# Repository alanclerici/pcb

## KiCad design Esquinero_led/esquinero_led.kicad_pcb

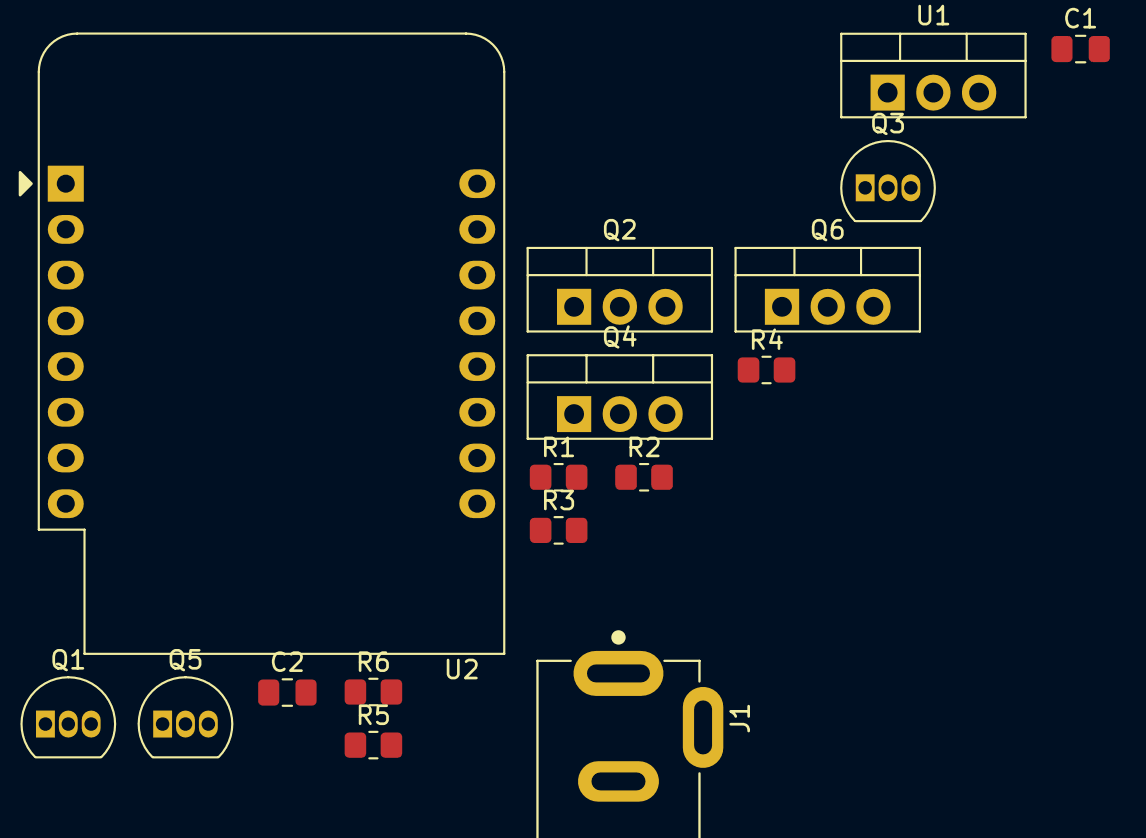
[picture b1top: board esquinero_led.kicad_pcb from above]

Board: 2 copper layers, 17 parts (0 on the bottom side), 9 nets, no tracks yet.

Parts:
C1, C2: 10uF; C_0805_2012Metric_Pad1.18x1.45mm_HandSolder
J1: PJ-002B; CUI_PJ-002B
Q1, Q3, Q5: BC548; TO-92_Inline
Q2, Q4, Q6: IRF540N; TO-220-3_Vertical
R1, R2, R3, R4, R5, R6: 10K; R_0805_2012Metric_Pad1.20x1.40mm_HandSolder
U1: LM7805_TO220; TO-220-3_Vertical
U2: WeMos_D1_mini; WEMOS_D1_mini_light

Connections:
+5V: C2.1, U1.3 (VO), U2.9 (5V)
+12V: C1.1, J1.1, R2.2, R4.2, R6.2, U1.1 (VI)
GND: C1.2, C2.2, J1.2, Q1.3 (E), Q2.3 (S), Q3.3 (E), Q4.3 (S), Q5.3 (E), Q6.3 (S), U1.2 (GND), U2.10 (GND)
unnamed: Q1.1 (C), Q2.1 (G), R2.1
unnamed: Q1.2 (B), R1.2
unnamed: Q3.1 (C), Q4.1 (G), R4.1
unnamed: Q3.2 (B), R3.2
unnamed: Q5.1 (C), Q6.1 (G), R6.1
unnamed: Q5.2 (B), R5.2

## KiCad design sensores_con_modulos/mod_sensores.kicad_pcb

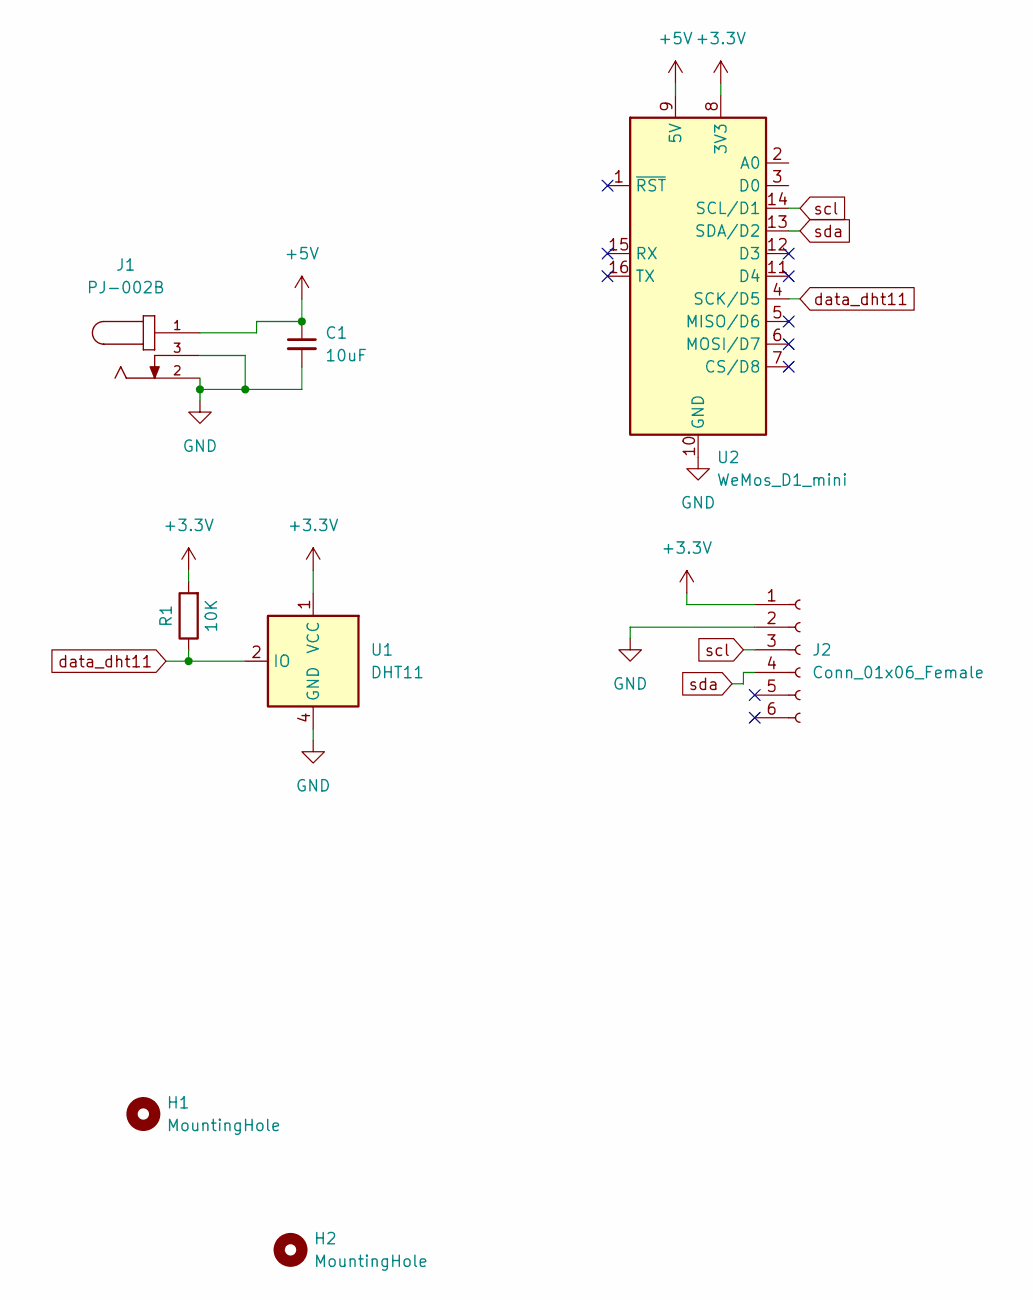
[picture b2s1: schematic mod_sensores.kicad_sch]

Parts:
C1: 10uF; CP_Radial_D5.0mm_P2.50mm
H1, H2: MountingHole; MountingHole_2.5mm
J1: PJ-002B; CUI_PJ-002B
J2: Conn_01x06_Female; PinHeader_1x06_P2.54mm_Vertical
R1: 10K; R_Axial_DIN0207_L6.3mm_D2.5mm_P7.62mm_Horizontal
U1: DHT11; Aosong_DHT11_5.5x12.0_P2.54mm
U2: WeMos_D1_mini; WEMOS_D1_mini_light

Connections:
+3.3V: J2.1, R1.2, U1.1 (VCC), U2.8 (3V3)
+5V: C1.1, J1.1, U2.9 (5V)
GND: C1.2, J1.2, J1.3, J2.2, U1.4 (GND), U2.10 (GND)
data_dht11: R1.1, U1.2 (IO), U2.4 (SCK/D5)
scl: J2.3, U2.14 (SCL/D1)
sda: J2.4, U2.13 (SDA/D2)

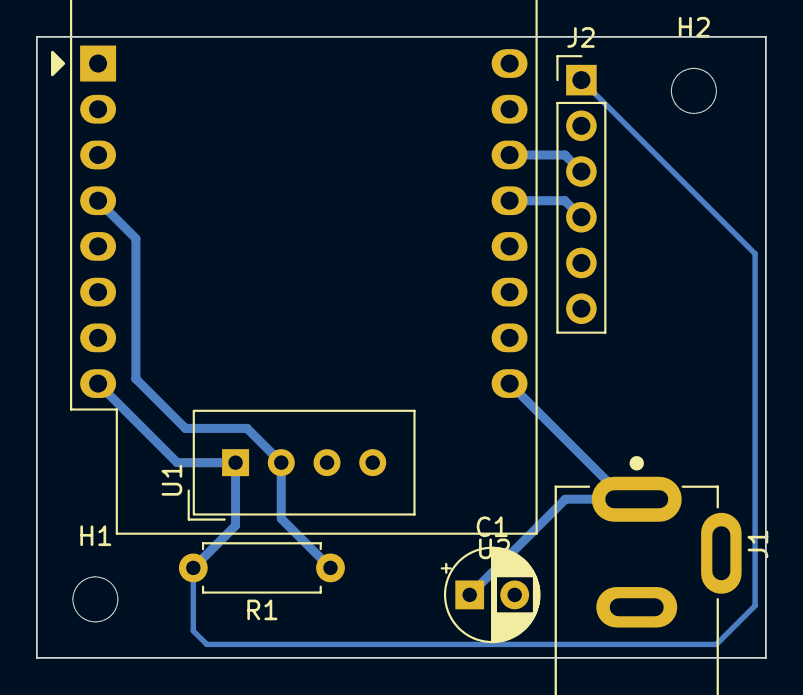
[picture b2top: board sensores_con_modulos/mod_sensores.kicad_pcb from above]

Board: 2 copper layers, 40.5 x 34.5 mm, 8 parts (0 on the bottom side), 6 nets.

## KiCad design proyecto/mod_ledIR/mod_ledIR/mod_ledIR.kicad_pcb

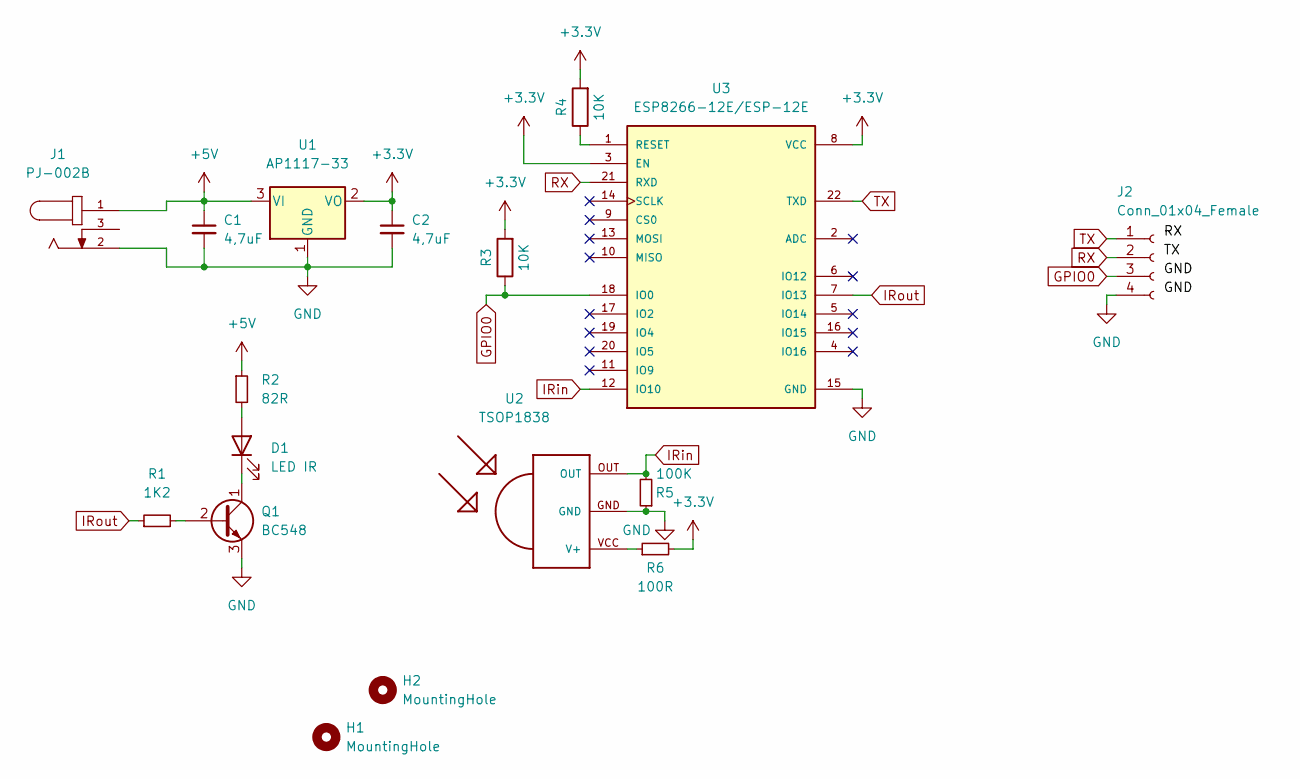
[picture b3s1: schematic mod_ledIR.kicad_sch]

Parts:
C1, C2: 4,7uF; C_0805_2012Metric_Pad1.18x1.45mm_HandSolder
D1: LED IR; LED_D5.0mm_Horizontal_O1.27mm_Z3.0mm
H1, H2: MountingHole; MountingHole_2.7mm
J1: PJ-002B; CUI_PJ-002B
J2: Conn_01x04_Female; PinHeader_1x04_P2.54mm_Vertical
Q1: BC548; TO-92_Inline
R1: 1K2; R_0805_2012Metric_Pad1.20x1.40mm_HandSolder
R2: 82R; R_Axial_DIN0207_L6.3mm_D2.5mm_P7.62mm_Horizontal
R3, R4: 10K; R_0805_2012Metric_Pad1.20x1.40mm_HandSolder
R5: 100K; R_0805_2012Metric_Pad1.20x1.40mm_HandSolder
R6: 100R; R_0805_2012Metric_Pad1.20x1.40mm_HandSolder
U1: AP1117-33; SOT-223-3_TabPin2
U2: TSOP1838; TSOP18XX
U3: ESP8266-12E/ESP-12E; XCVR_ESP8266-12E/ESP-12E

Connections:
+3.3V: C2.1, R3.2, R4.2, R6.2, U1.2 (VO), U3.3 (EN), U3.8 (VCC)
+5V: C1.1, J1.1, R2.1, U1.3 (VI)
GND: C1.2, C2.2, J1.2, J2.4, Q1.3 (E), R5.1, U1.1 (GND), U2.GND, U3.15 (GND)
GPIO0: J2.3, R3.1, U3.18 (IO0)
IRin: R5.2, U2.OUT, U3.12 (IO10)
IRout: R1.1, U3.7 (IO13)
unnamed: D1.1 (K), Q1.1 (C)
unnamed: D1.2 (A), R2.2
unnamed: Q1.2 (B), R1.2
unnamed: R4.1, U3.1 (RESET)
unnamed: R6.1, U2.VCC (V+)
RX: J2.2, U3.21 (RXD)
TX: J2.1, U3.22 (TXD)

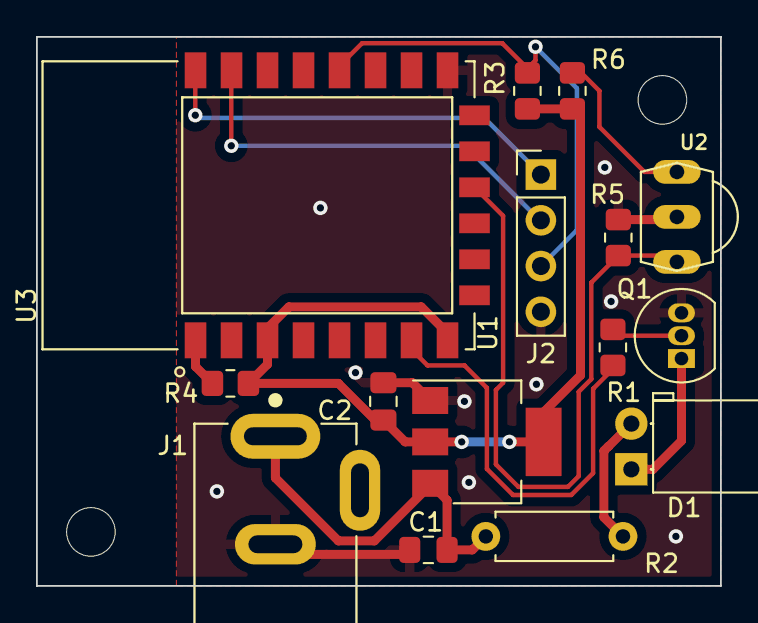
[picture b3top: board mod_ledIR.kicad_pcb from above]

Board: 2 copper layers, 38.0 x 30.5 mm, 17 parts (0 on the bottom side), 13 nets.

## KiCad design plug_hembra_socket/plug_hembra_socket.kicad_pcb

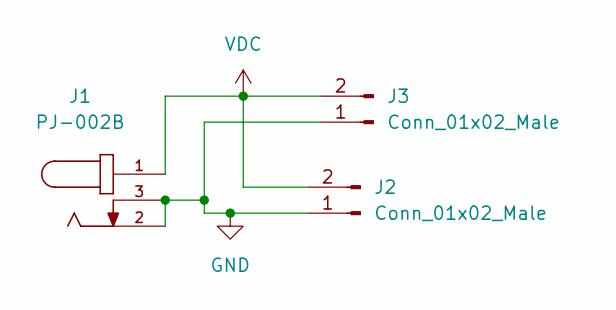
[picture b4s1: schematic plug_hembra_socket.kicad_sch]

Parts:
J1: PJ-002B; CUI_PJ-002B
J2, J3: Conn_01x02_Male; PinHeader_1x02_P2.54mm_Vertical

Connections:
GND: J1.2, J1.3, J2.1, J3.1
VDC: J1.1, J2.2, J3.2

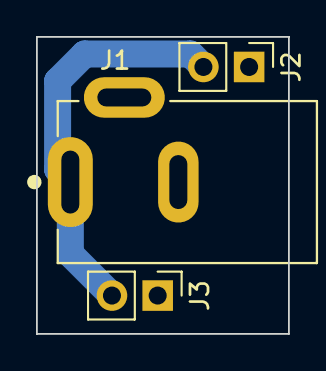
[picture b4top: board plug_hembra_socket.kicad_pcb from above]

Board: 2 copper layers, 14.0 x 16.5 mm, 3 parts (0 on the bottom side), 2 nets.

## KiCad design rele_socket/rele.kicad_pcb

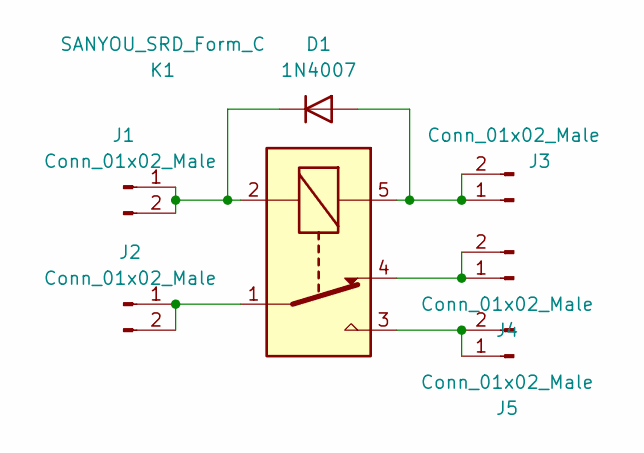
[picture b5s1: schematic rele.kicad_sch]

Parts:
D1: 1N4007; D_DO-41_SOD81_P10.16mm_Horizontal
J1, J2, J3, J4, J5: Conn_01x02_Male; PinHeader_1x02_P2.54mm_Vertical
K1: SANYOU_SRD_Form_C; Relay_SPDT_SANYOU_SRD_Series_Form_C

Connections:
unnamed: D1.1 (K), J1.1, J1.2, K1.2
unnamed: D1.2 (A), J3.1, J3.2, K1.5
unnamed: J2.1, J2.2, K1.1
unnamed: J4.1, J4.2, K1.4
unnamed: J5.1, J5.2, K1.3

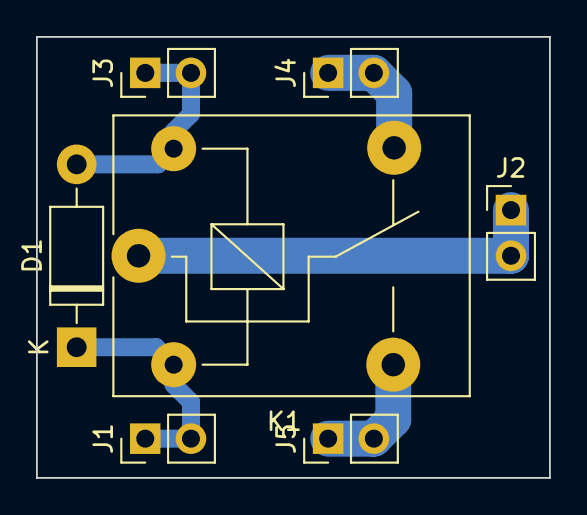
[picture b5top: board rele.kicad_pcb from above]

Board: 2 copper layers, 28.5 x 24.5 mm, 7 parts (0 on the bottom side), 5 nets.

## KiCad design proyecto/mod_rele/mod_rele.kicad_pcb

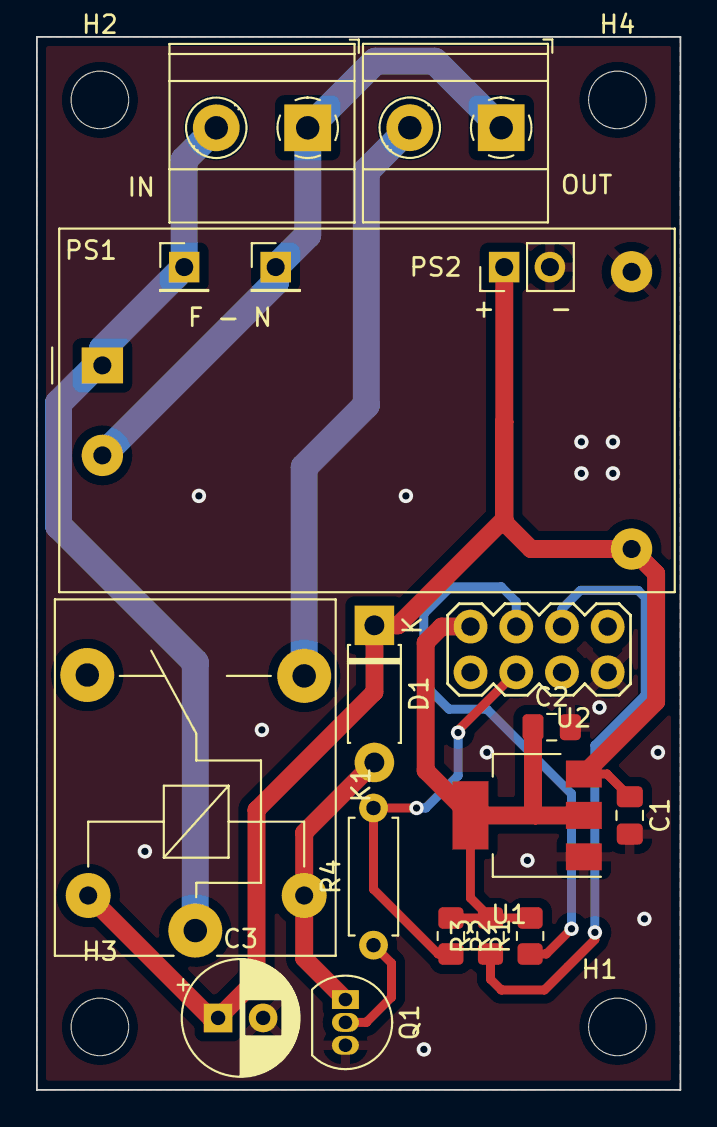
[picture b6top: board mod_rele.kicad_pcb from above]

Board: 2 copper layers, 35.8 x 58.5 mm, 22 parts (0 on the bottom side), 11 nets.

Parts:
+    -: Conn_01x02_Male; PinHeader_1x02_P2.54mm_Vertical
C1, C2: 4,7uF; C_0805_2012Metric_Pad1.18x1.45mm_HandSolder
C3: 220uF; CP_Radial_D6.3mm_P2.50mm
D1: 1N4007; D_DO-41_SOD81_P7.62mm_Horizontal
F - N: Conn_01x01_Male; PinHeader_1x01_P2.54mm_Vertical
H1, H2, H3, H4: MountingHole; MountingHole_3.2mm_M3
IN: Screw_Terminal_01x02; TerminalBlock_Phoenix_MKDS-1,5-2-5.08_1x02_P5.08mm_Horizont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
K1: SANYOU_SRD_Form_C; Relay_SPDT_SANYOU_SRD_Series_Form_C
OUT: Screw_Terminal_01x02; TerminalBlock_Phoenix_MKDS-1,5-2-5.08_1x02_P5.08mm_Horizont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
PS1: HLK-PM01; Converter_ACDC_HiLink_HLK-PMxx
PS2: Conn_01x01_Male; PinHeader_1x01_P2.54mm_Vertical
Q1: BC548; TO-92_Inline
R1, R2, R3: 10K; R_0805_2012Metric_Pad1.20x1.40mm_HandSolder
R4: 3K9; R_Axial_DIN0207_L6.3mm_D2.5mm_P7.62mm_Horizontal
U1: AP1117-33; SOT-223-3_TabPin2
U2: ESP-01

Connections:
+3.3V: C2.1, R1.2, R2.1, R3.2, U1.2 (VO), U2.7 (VCC)
+5V: + -.1, C1.1, C3.1, D1.1 (K), K1.5, PS1.4 (+Vout), U1.3 (VI)
AC: F - N.1, IN.2, K1.1, PS1.1 (AC/L)
Earth: IN.1, OUT.1, PS1.2 (AC/N), PS2.1
GND: + -.2, C1.2, C2.2, C3.2, PS1.3 (-Vout), Q1.3 (E), U1.1 (GND), U2.2 (GND)
unnamed: D1.2 (A), K1.2, Q1.1 (C)
unnamed: K1.3, OUT.2
unnamed: Q1.2 (B), R4.1
unnamed: R1.1, U2.5 (RST)
unnamed: R3.1, U2.3 (PD)
out: R2.2, R4.2, U2.6 (GPIO0)

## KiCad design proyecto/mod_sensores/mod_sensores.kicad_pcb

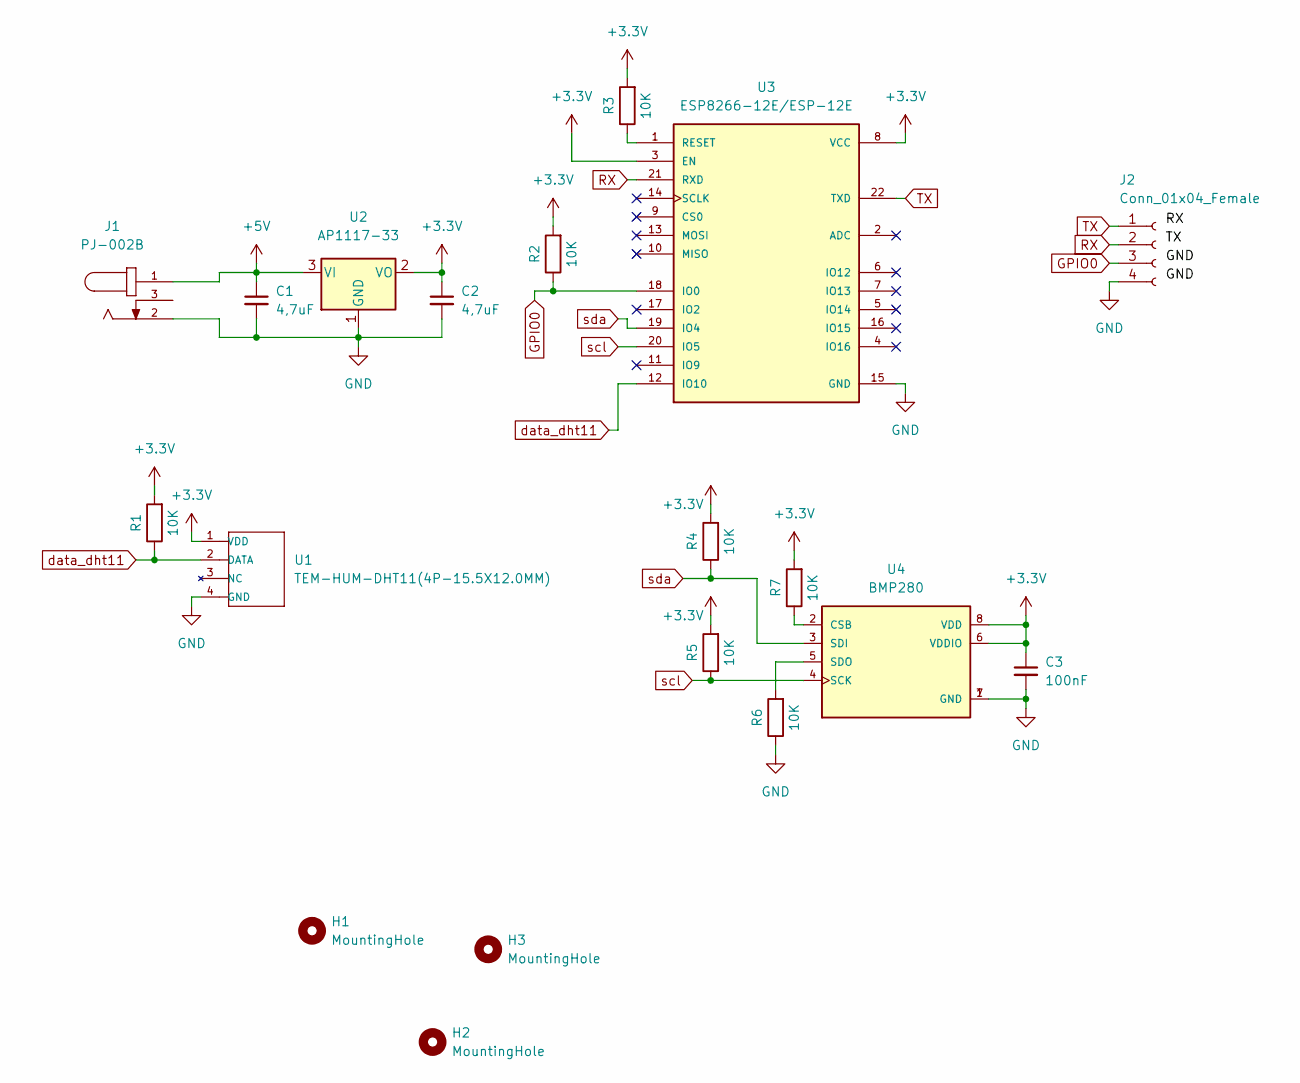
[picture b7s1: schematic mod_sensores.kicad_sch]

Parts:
C1, C2: 4,7uF; C_0805_2012Metric_Pad1.18x1.45mm_HandSolder
C3: 100nF; C_0805_2012Metric_Pad1.18x1.45mm_HandSolder
H1, H2, H3: MountingHole; MountingHole_2.5mm
J1: PJ-002B; CUI_PJ-002B
J2: Conn_01x04_Female; PinHeader_1x04_P2.54mm_Vertical
R1, R2, R3, R4, R5, R6, R7: 10K; R_0805_2012Metric_Pad1.20x1.40mm_HandSolder
U1: TEM-HUM-DHT11(4P-15.5X12.0MM); SNR4-2.54-15.5X12.0X5.5MM; MPN DHT11
U2: AP1117-33; SOT-223-3_TabPin2
U3: ESP8266-12E/ESP-12E; XCVR_ESP8266-12E/ESP-12E
U4: BMP280; XDCR_BMP280; PART_REV 1.19

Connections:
+3.3V: C2.1, C3.1, R1.2, R2.2, R3.2, R4.2, R5.2, R7.2, U1.1 (VDD), U2.2 (VO), U3.3 (EN), U3.8 (VCC), U4.6 (VDDIO), U4.8 (VDD)
+5V: C1.1, J1.1, U2.3 (VI)
GND: C1.2, C2.2, C3.2, J1.2, J2.4, R6.1, U1.4 (GND), U2.1 (GND), U3.15 (GND), U4.1 (GND), U4.7 (GND)
GPIO0: J2.3, R2.1, U3.18 (IO0)
unnamed: R3.1, U3.1 (RESET)
unnamed: R6.2, U4.5 (SDO)
unnamed: R7.1, U4.2 (CSB)
RX: J2.2, U3.21 (RXD)
TX: J2.1, U3.22 (TXD)
data_dht11: R1.1, U1.2 (DATA), U3.12 (IO10)
scl: R5.1, U3.20 (IO5), U4.4 (SCK)
sda: R4.1, U3.19 (IO4), U4.3 (SDI)

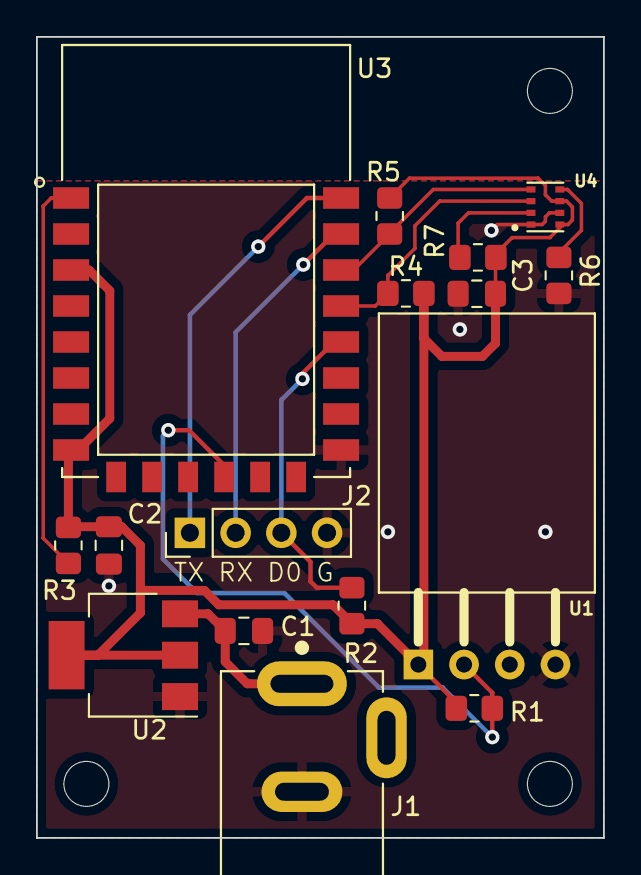
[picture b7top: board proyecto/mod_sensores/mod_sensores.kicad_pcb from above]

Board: 2 copper layers, 31.5 x 44.5 mm, 19 parts (0 on the bottom side), 12 nets.

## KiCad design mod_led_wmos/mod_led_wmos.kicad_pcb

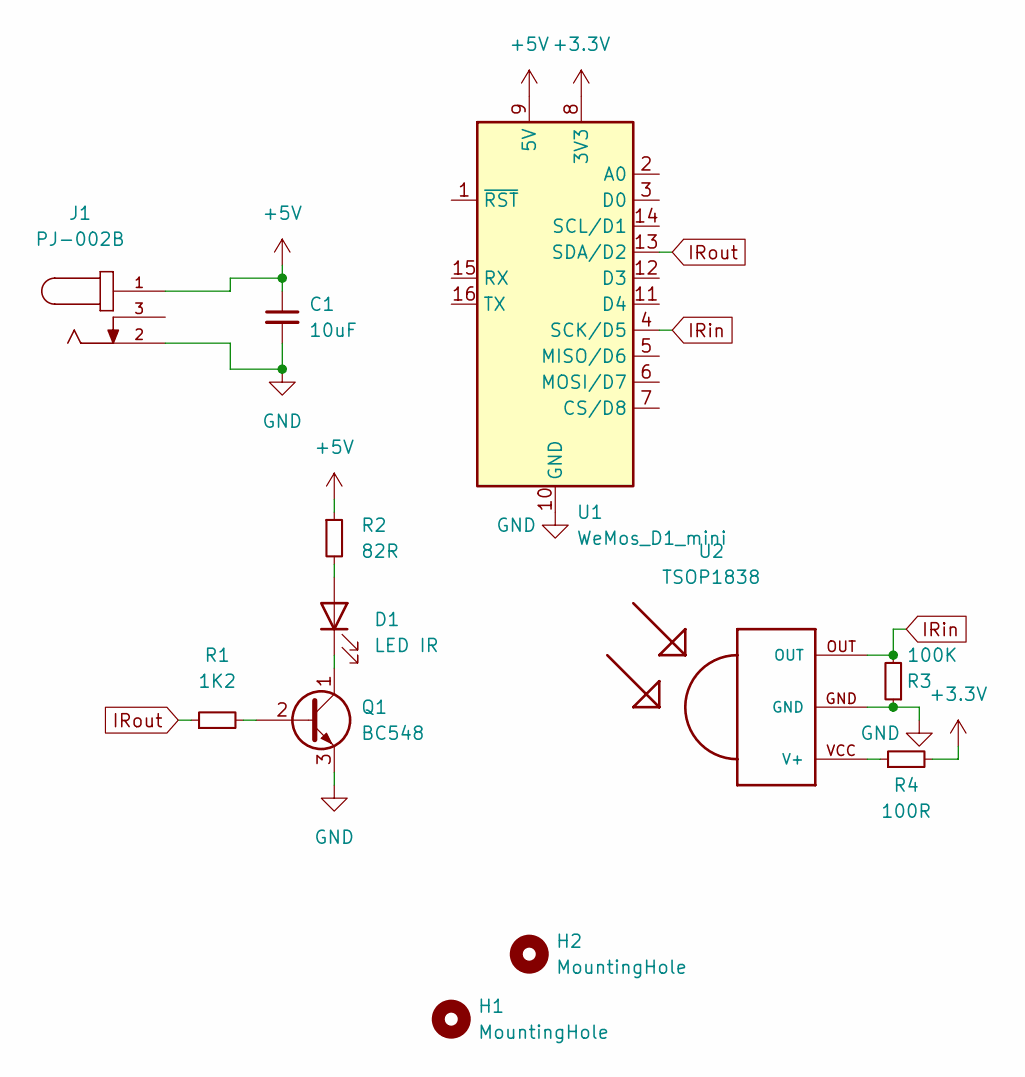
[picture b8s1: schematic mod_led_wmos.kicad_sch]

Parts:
C1: 10uF; CP_Radial_D5.0mm_P2.50mm
D1: LED IR; LED_D5.0mm_Horizontal_O1.27mm_Z3.0mm
H1, H2: MountingHole; MountingHole_2.7mm
J1: PJ-002B; CUI_PJ-002B
Q1: BC548; TO-92_Inline
R1: 1K2; R_Axial_DIN0207_L6.3mm_D2.5mm_P7.62mm_Horizontal
R2: 82R; R_Axial_DIN0207_L6.3mm_D2.5mm_P7.62mm_Horizontal
R3: 100K; R_Axial_DIN0207_L6.3mm_D2.5mm_P7.62mm_Horizontal
R4: 100R; R_Axial_DIN0207_L6.3mm_D2.5mm_P7.62mm_Horizontal
U1: WeMos_D1_mini; WEMOS_D1_mini_light
U2: TSOP1838; TSOP18XX

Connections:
+3.3V: R4.2, U1.8 (3V3)
+5V: C1.1, J1.1, R2.1, U1.9 (5V)
GND: C1.2, J1.2, Q1.3 (E), R3.1, U1.10 (GND), U2.GND
IRin: R3.2, U1.4 (SCK/D5), U2.OUT
IRout: R1.1, U1.13 (SDA/D2)
unnamed: D1.1 (K), Q1.1 (C)
unnamed: D1.2 (A), R2.2
unnamed: Q1.2 (B), R1.2
unnamed: R4.1, U2.VCC (V+)

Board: 2 copper layers, 12 parts (0 on the bottom side), 9 nets, no tracks yet.

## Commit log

2023-02-16 inicio
2023-02-16 ajuste carpetas
